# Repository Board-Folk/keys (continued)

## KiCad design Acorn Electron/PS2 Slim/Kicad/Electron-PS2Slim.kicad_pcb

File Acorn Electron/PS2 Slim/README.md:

# Acorn Electron PS/2 Slim v1

A keyboard interface for the Acorn Electron based on C64keyboard by Robert VanHazinga using an ATMEGA328 and an MT8816 switch chip. This is a surface mount board designed to fit inside the Electron's case
with the original keyboard still connected. The PS/2 socket sits a the hole of the original UHF modulator - requires the modulator to be removed for fitting.

The break key is 'Print Screen'.

* BOM

iBOM for the board.

* Export

Exported binaries and batch files for programming the ATMEGA328. Please modify the batch files to suite your avrdude configuration.

* Gerber

Gerbers and gerber zip file for production.

* Kicad

Kicad project for the board.

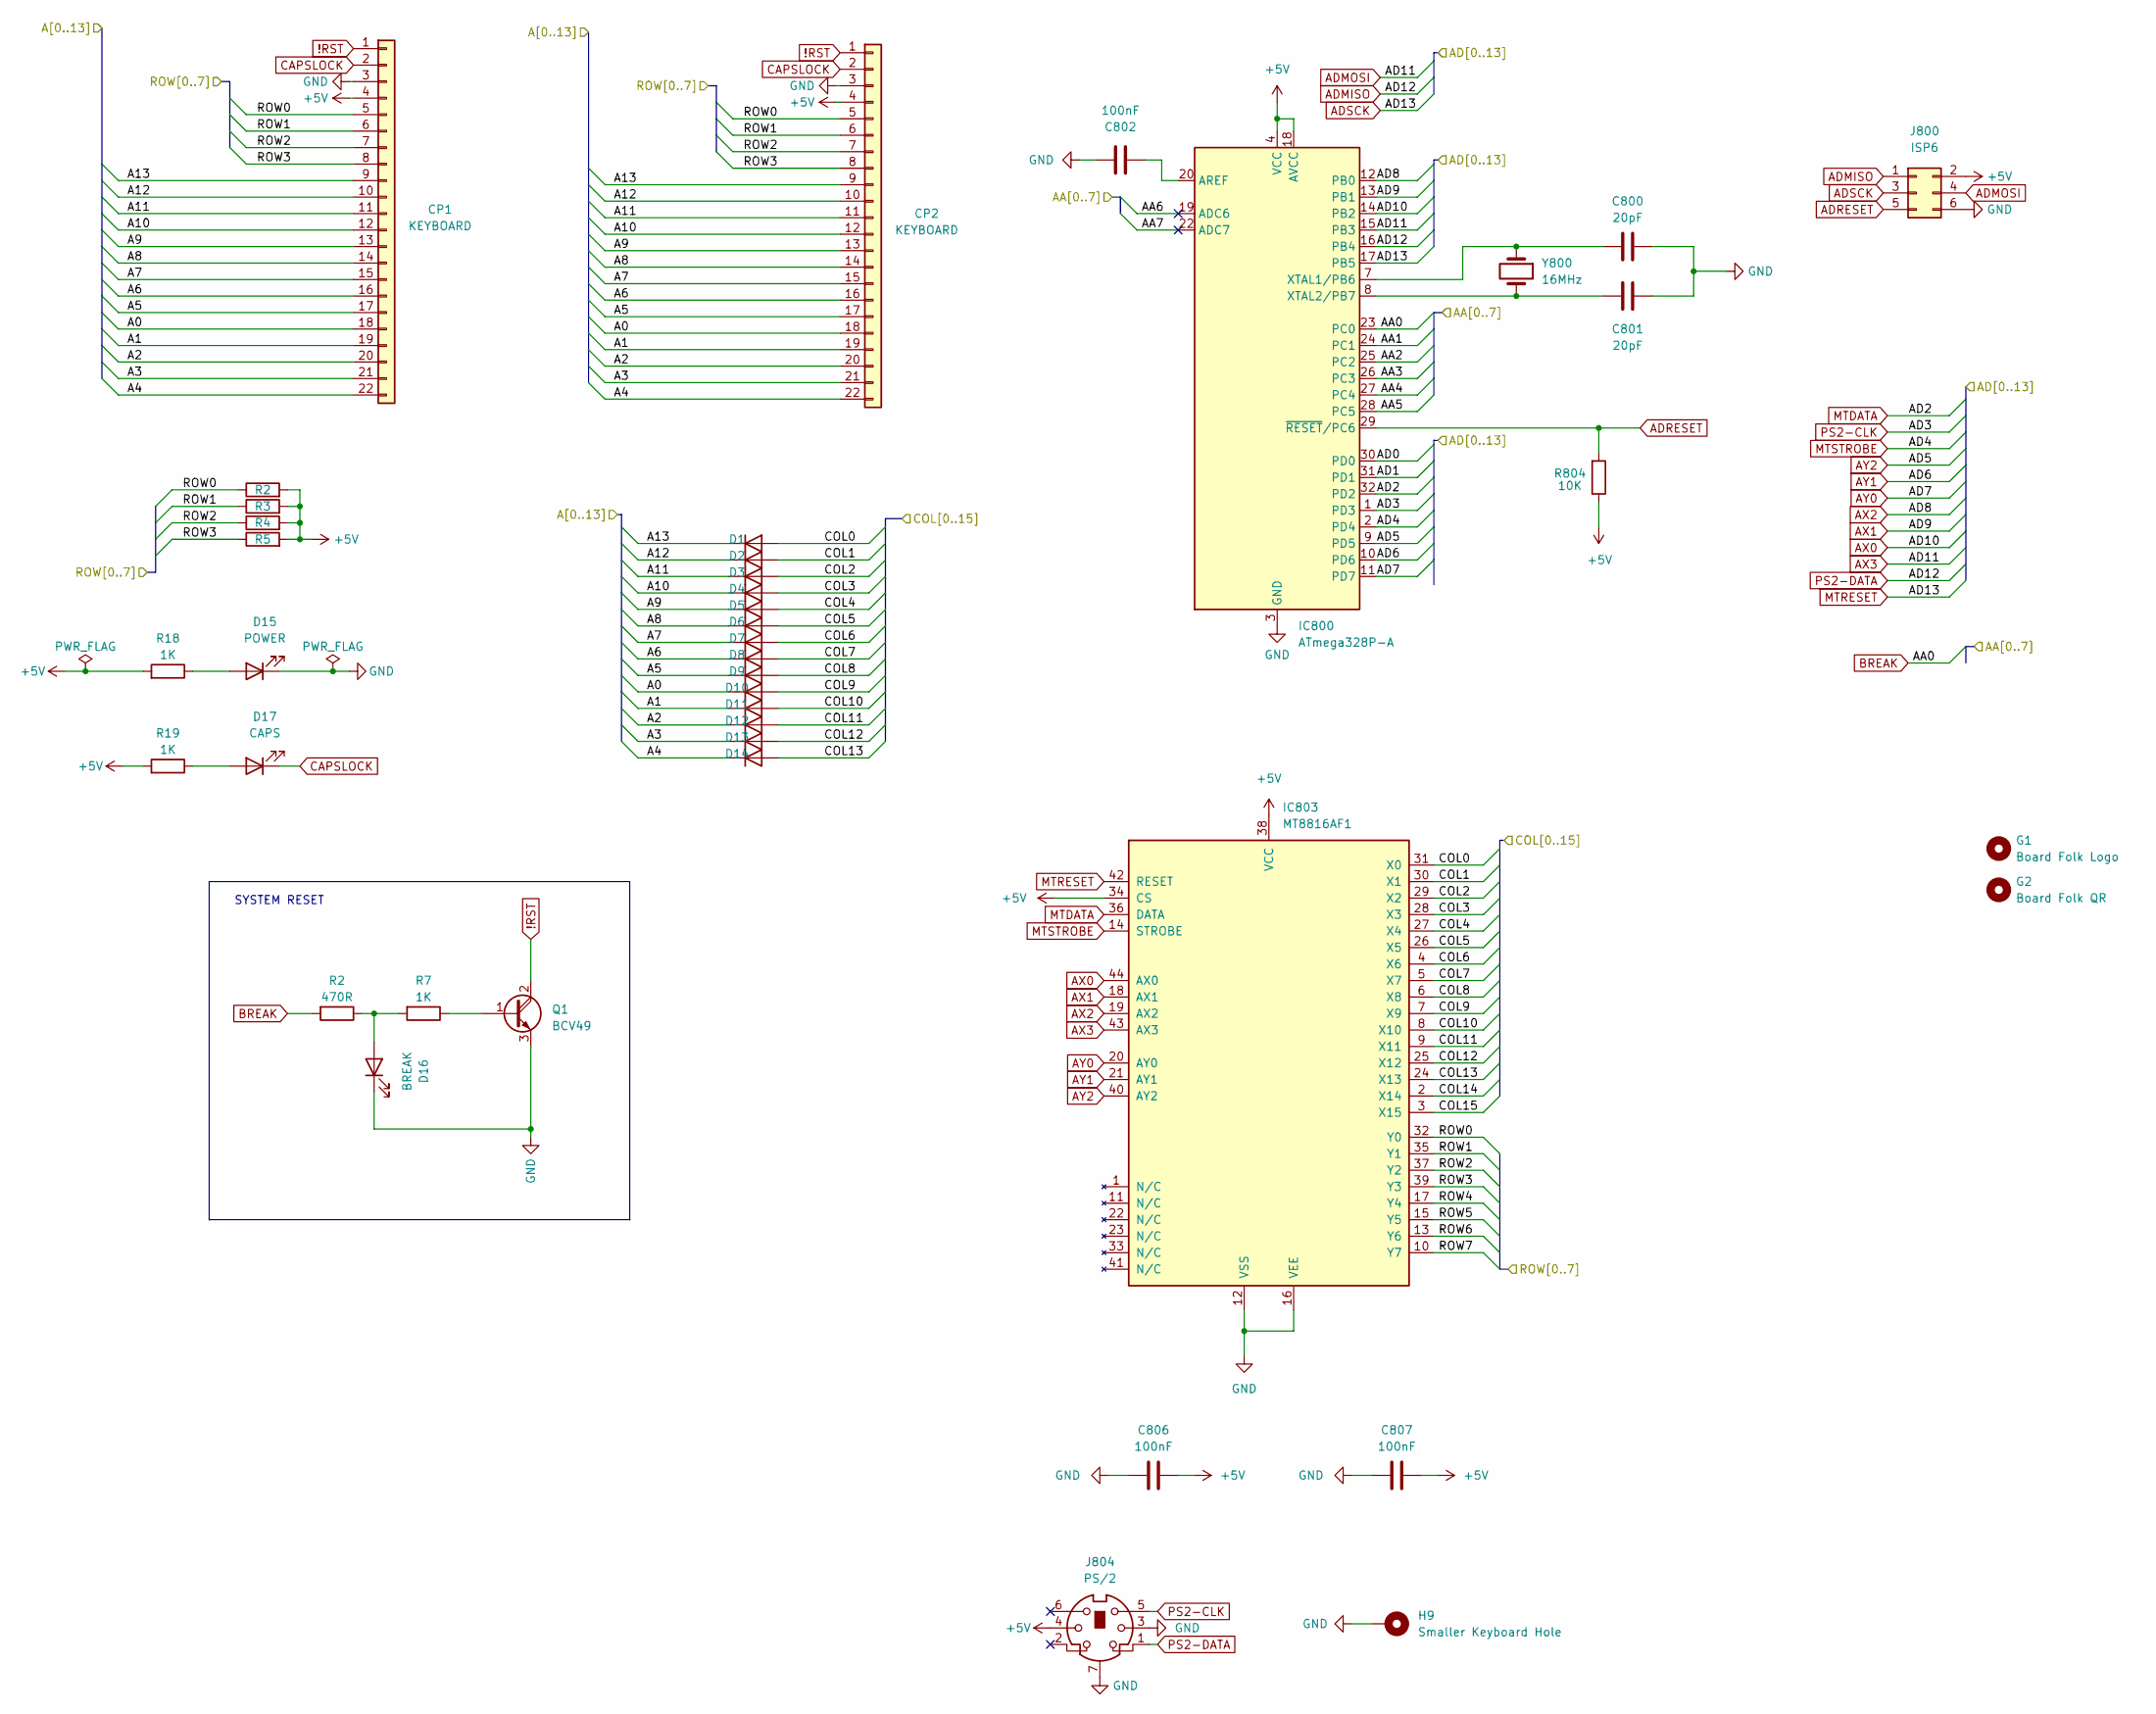
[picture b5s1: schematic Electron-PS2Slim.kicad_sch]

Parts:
C800, C801: 20pF; C_0805_2012Metric
C802, C806, C807: 100nF; C_0805_2012Metric
CP1, CP2: KEYBOARD; PinHeader_1x22_P2.54mm_Vertical
D1, D2, D3, D4, D5, D6, D7, D8, D9, D10, D11, D12, D13, D14: 1N4148; MINIDIODE
D15: POWER; LED_1206_3216Metric
D16: BREAK; LED_1206_3216Metric
D17: CAPS; LED_1206_3216Metric
G1: Board Folk Logo; BF8
G2: Board Folk QR; bf_qr8
H9: Smaller Keyboard Hole; MountingHole_2.2mm_M2_DIN965_Pad
IC800: ATmega328P-A; TQFP-32_7x7mm_P0.8mm
IC803: MT8816AF1; TQFP-44_10x10mm_P0.8mm
J800: ISP6; PinHeader_2x03_P2.54mm_Vertical
J804: PS/2; Connector_Mini-DIN_Female_6Pin_2rows
Q1: BCV49; SOT-89-3
R2, R3, R4, R5: 15K; R_0805_2012Metric
R7, R18, R19: 1K; R_0805_2012Metric
R804: 10K; R_0805_2012Metric
Y800: 16MHz; Crystal_HC49-U_Vertical

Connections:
!RST: CP1.1, CP2.1, Q1.2 (C)
/A0: CP1.18, CP2.18, D10.1 (K)
/A1: CP1.19, CP2.19, D11.1 (K)
/A2: CP1.20, CP2.20, D12.1 (K)
/A3: CP1.21, CP2.21, D13.1 (K)
/A4: CP1.22, CP2.22, D14.1 (K)
/A5: CP1.17, CP2.17, D9.1 (K)
/A6: CP1.16, CP2.16, D8.1 (K)
/A7: CP1.15, CP2.15, D7.1 (K)
/A8: CP1.14, CP2.14, D6.1 (K)
/A9: CP1.13, CP2.13, D5.1 (K)
/A10: CP1.12, CP2.12, D4.1 (K)
/A11: CP1.11, CP2.11, D3.1 (K)
/A12: CP1.10, CP2.10, D2.1 (K)
/A13: CP1.9, CP2.9, D1.1 (K)
/AA1: IC800.24 (PC1)
/AA2: IC800.25 (PC2)
/AA3: IC800.26 (PC3)
/AA4: IC800.27 (PC4)
/AA5: IC800.28 (PC5)
/AA6: IC800.19 (ADC6)
/AA7: IC800.22 (ADC7)
/AD0: IC800.30 (PD0)
/AD1: IC800.31 (PD1)
/COL0: D1.2 (A), IC803.31 (X0)
/COL1: D2.2 (A), IC803.30 (X1)
/COL2: D3.2 (A), IC803.29 (X2)
/COL3: D4.2 (A), IC803.28 (X3)
/COL4: D5.2 (A), IC803.27 (X4)
/COL5: D6.2 (A), IC803.26 (X5)
/COL6: D7.2 (A), IC803.4 (X6)
/COL7: D8.2 (A), IC803.5 (X7)
/COL8: D9.2 (A), IC803.6 (X8)
/COL9: D10.2 (A), IC803.7 (X9)
/COL10: D11.2 (A), IC803.8 (X10)
/COL11: D12.2 (A), IC803.9 (X11)
/COL12: D13.2 (A), IC803.25 (X12)
/COL13: D14.2 (A), IC803.24 (X13)
/COL14: IC803.2 (X14)
/COL15: IC803.3 (X15)
/ROW1: CP1.6, CP2.6, IC803.35 (Y1), R3.1
/ROW2: CP1.7, CP2.7, IC803.37 (Y2), R4.1
/ROW3: CP1.8, CP2.8, IC803.39 (Y3), R5.1
/ROW4: IC803.17 (Y4)
/ROW5: IC803.15 (Y5)
/ROW6: IC803.13 (Y6)
/ROW7: IC803.10 (Y7)
ADMISO: IC800.16 (PB4), J800.1, J804.1
ADMOSI: IC800.15 (PB3), IC803.43 (AX3), J800.4
ADRESET: IC800.29 (~RESET/PC6), J800.5, R804.2
ADSCK: IC800.17 (PB5), IC803.42 (RESET), J800.3
AX0: IC800.14 (PB2), IC803.44 (AX0)
AX1: IC800.13 (PB1), IC803.18 (AX1)
AX2: IC800.12 (PB0), IC803.19 (AX2)
AY0: IC800.11 (PD7), IC803.20 (AY0)
AY1: IC800.10 (PD6), IC803.21 (AY1)
AY2: IC800.9 (PD5), IC803.40 (AY2)
CAPSLOCK: CP1.2, CP2.2, D17.1 (K)
GND: C800.2, C801.2, C802.2, C806.1, C807.1, CP1.3, CP2.3, D15.1 (K), D16.1 (K), H9.1, IC800.3 (GND), IC800.5 (GND), IC800.21 (GND), IC803.12 (VSS), IC803.16 (VEE), J800.6, J804.3, J804.7, Q1.3 (E)
MTDATA: IC800.32 (PD2), IC803.36 (DATA)
MTSTROBE: IC800.2 (PD4), IC803.14 (STROBE)
unnamed: D15.2 (A), R18.1
unnamed: D17.2 (A), R19.1
unnamed: C802.1, IC800.20 (AREF)
unnamed: C800.1, IC800.7 (XTAL1/PB6), Y800.1
unnamed: C801.1, IC800.8 (XTAL2/PB7), Y800.2
unnamed 66: Q1.1 (B); also elsewhere on the board
PS2-CLK: IC800.1 (PD3), J804.5

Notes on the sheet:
SYSTEM RESET

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
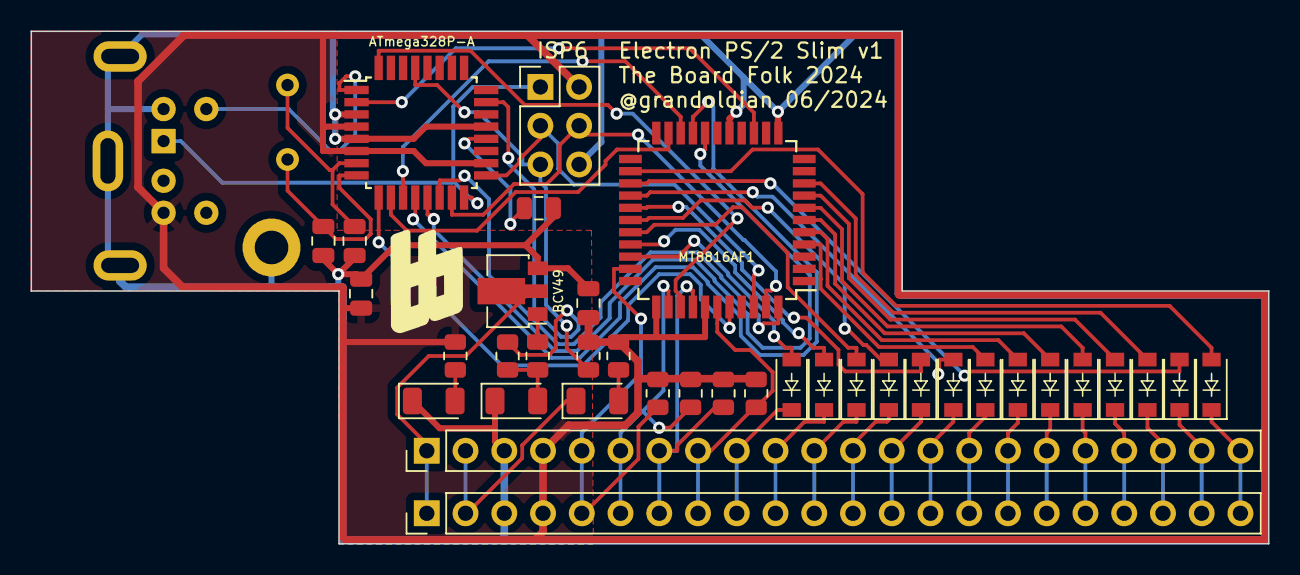
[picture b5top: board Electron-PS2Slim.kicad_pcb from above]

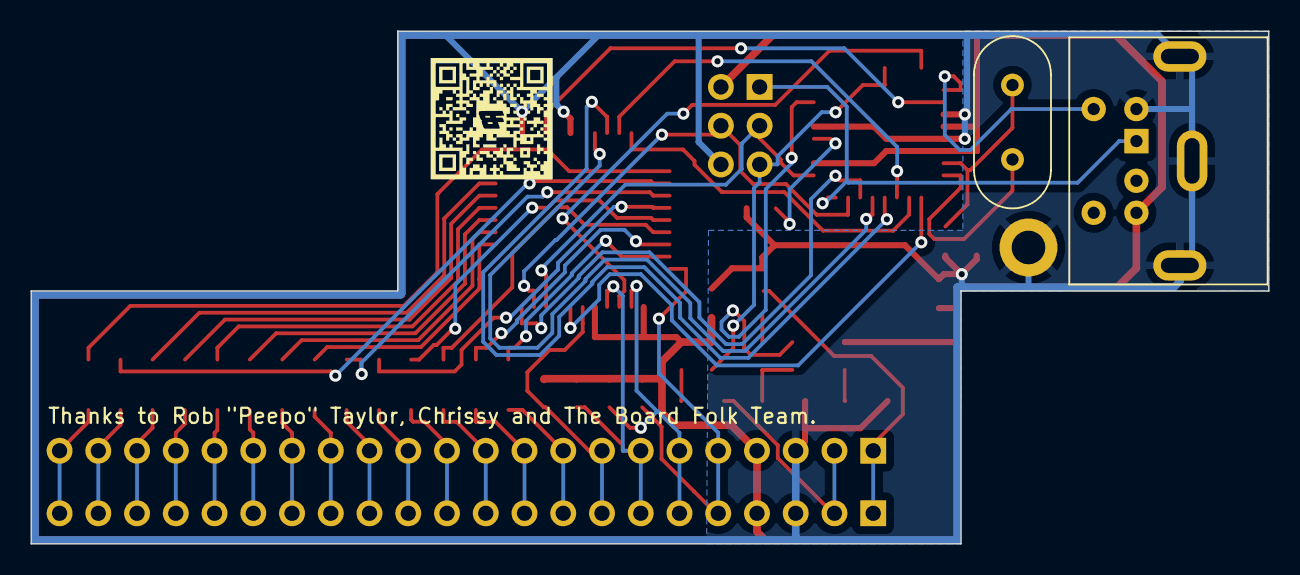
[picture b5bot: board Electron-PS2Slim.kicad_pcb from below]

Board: 2 copper layers, 81.1 x 33.6 mm, 42 parts (3 on the bottom side), 57 nets.

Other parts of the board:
R16: 470R; R_0805_2012Metric
R17: 1K; R_0805_2012Metric

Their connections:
unnamed 66: R17.1; also elsewhere on the board

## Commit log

2024-06-29 Baseline
2025-11-04 BBC Master MX Keyboard
2025-11-04 Rename to Master MX to MX
2025-11-04 Master Replica Keyboard
2026-05-26 add Acorn Atom keyboard
